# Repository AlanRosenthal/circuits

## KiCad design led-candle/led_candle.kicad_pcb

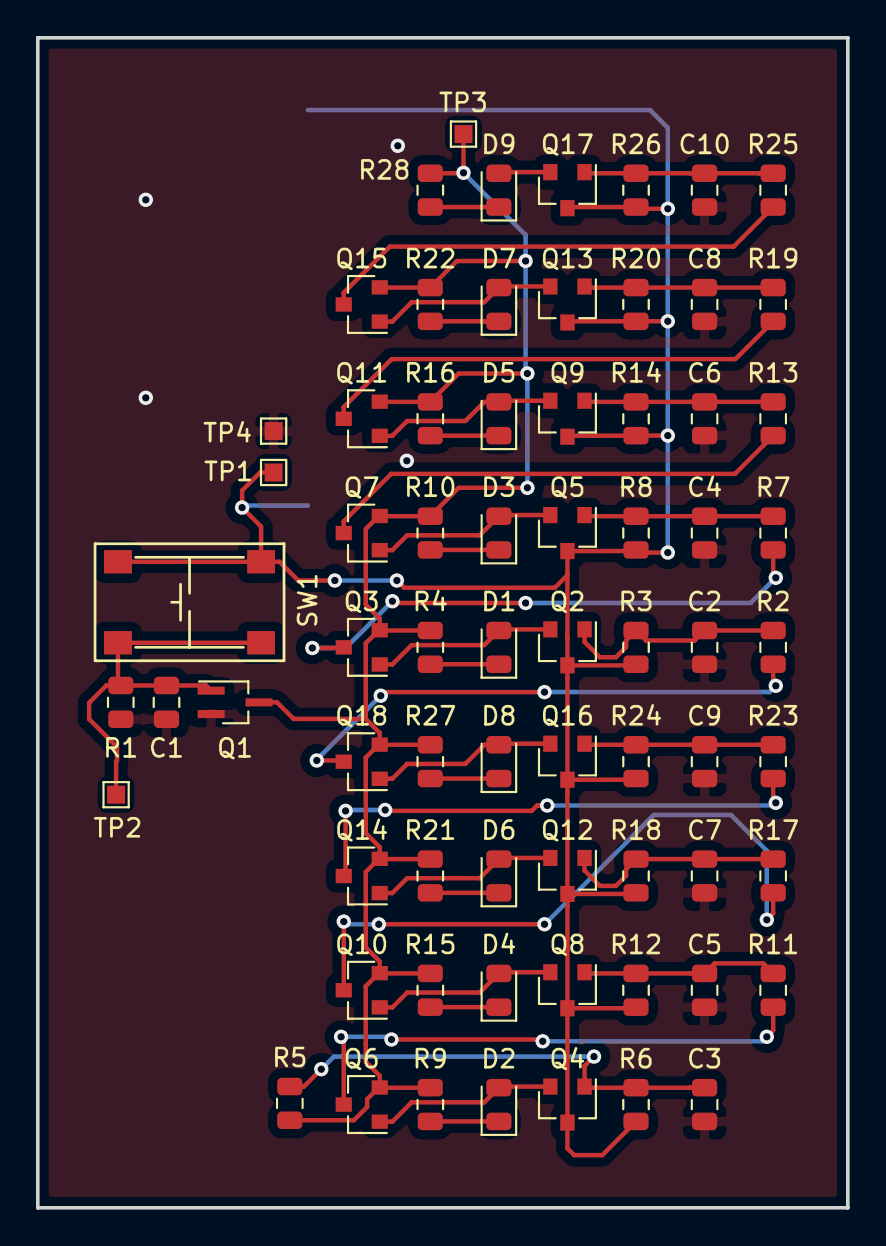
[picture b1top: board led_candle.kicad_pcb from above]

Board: 2 copper layers, 45.0 x 65.0 mm, 71 parts (1 on the bottom side), 39 nets.

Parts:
BT1: Battery_Cell; BK-912
C1: 51u; C_0805_2012Metric
C2, C3, C4, C5, C6, C7, C8, C9, C10: 10u; C_0805_2012Metric
D1, D2, D3, D4, D5, D6, D7, D8, D9: LED; LED_0805_2012Metric
Q1: RTF015N03; SOT-323_SC-70_Handsoldering
Q2, Q4, Q5, Q8, Q9, Q12, Q13, Q16, Q17: RTR020P02FRA; SOT-23
Q3, Q6, Q7, Q10, Q11, Q14, Q15, Q18: RK7002BM; SOT-23
R1: 1M; R_0805_2012Metric
R2, R5, R7, R11, R13, R17, R19, R23, R25: 120k; R_0805_2012Metric
R3, R6, R8, R12, R14, R18, R20, R24, R26: 2M; R_0805_2012Metric
R4, R9, R10, R15, R16, R21, R22, R27, R28: 50; R_0805_2012Metric
SW1: SW_Push; PTS645SM43SMTR92
TP1: 3.3V; TestPoint_Pad_1.0x1.0mm
TP2: 3.3V_RC; TestPoint_Pad_1.0x1.0mm
TP3: VDD; TestPoint_Pad_1.0x1.0mm
TP4: GND; TestPoint_Pad_1.0x1.0mm

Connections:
+3V3: BT1.1, Q2.3, Q4.3, Q5.3, Q8.3, Q9.3, Q12.3, Q13.3, Q16.3, Q17.3, R3.2, R6.2, R8.2, R12.2, R14.2, R18.2, R20.2, R24.2, R26.2, SW1.1, TP1.1
GND: BT1.2, C1.2, C2.2, C3.2, C4.2, C5.2, C6.2, C7.2, C8.2, C9.2, C10.2, Q1.2, R1.2, TP4.1
unnamed: C1.1, Q1.1, R1.1, SW1.2, TP2.1
unnamed: C2.1, Q2.1, R2.1, R3.1
unnamed: C3.1, Q4.1, R5.1, R6.1
unnamed: C4.1, Q5.1, R7.1, R8.1
unnamed: C5.1, Q8.1, R11.1, R12.1
unnamed: C6.1, Q9.1, R13.1, R14.1
unnamed: C7.1, Q12.1, R17.1, R18.1
unnamed: C8.1, Q13.1, R19.1, R20.1
unnamed: C9.1, Q16.1, R23.1, R24.1
unnamed: C10.1, Q17.1, R25.1, R26.1
unnamed: D1.1, R4.2
unnamed: D1.2, Q2.2, Q3.1
unnamed: D2.1, R9.2
unnamed: D2.2, Q4.2, Q6.1
unnamed: D3.1, R10.2
unnamed: D3.2, Q5.2, Q7.1
unnamed: D4.1, R15.2
unnamed: D4.2, Q8.2, Q10.1
unnamed: D5.1, R16.2
unnamed: D5.2, Q9.2, Q11.1
unnamed: D6.1, R21.2
unnamed: D6.2, Q12.2, Q14.1
unnamed: D7.1, R22.2
unnamed: D7.2, Q13.2, Q15.1
unnamed: D8.1, R27.2
unnamed: D8.2, Q16.2, Q18.1
unnamed: D9.1, R28.2
unnamed: D9.2, Q17.2
unnamed: Q3.3, R7.2
unnamed: Q6.3, R11.2
unnamed: Q7.3, R13.2
unnamed: Q10.3, R17.2
unnamed: Q11.3, R19.2
unnamed: Q14.3, R23.2
unnamed: Q15.3, R25.2
VDD: Q1.3, Q3.2, Q6.2, Q7.2, Q10.2, Q11.2, Q14.2, Q15.2, Q18.2, R4.1, R5.2, R9.1, R10.1, R15.1, R16.1, R21.1, R22.1, R27.1, R28.1, TP3.1
Vd4: Q18.3, R2.2

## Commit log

2018-10-23 Inital commit of LED Candle v0.1
